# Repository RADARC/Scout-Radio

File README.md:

# Scout-Radio
Si4732 and Raspberry Pi Pico Radio device for Scouts to build and use to gain badges

Reading and District Amateur Radio Club works withl local Scouts groups and help them in support of their badges and activities

## Objectives:
<ul>
<li>Design and build a radio device with can support Scouts in the following badges
<ul>
<li>[Electronics](https://www.scouts.org.uk/scouts/activity-badges/electronics/)</li>
<li>[Communicator](https://www.scouts.org.uk/scouts/activity-badges/communicator/)</li>
</ul>
<li>Involve Scouts in radio activities</li>
<li>Potential Sponsorship and incresaed local community technology support for Scouts</li>
<li>Interesting Project for RADARC Constructors</li>
<li>Have Fun!</li>
</ul>

## Design Specification
Derived from the RLab Reading Hackspace [Project Athena](https://github.com/reading-hackspace/project-athena)
<ul>
<li>Microprocessor design based on Raspberry Pi Pico Microcontroller</li>
<li>Programmable firmware in CircuitPython and other programming languages via USB</li>
<li>On Board AM and FM Radio</li>
<li>Loudspeaker and audio output</li>
<li>Rotary Encoder and control buttons</li>
<li>Battery powered 3 off AAA, or LiPo with on board charger from USB</li>
<li>Audio output jack</li>
<li>Mixture of surface mount and through hole components. Some components can be factory assembled</li>
<li>Colour LCD display integral</li> 
<li>Optional GPS module</li>
<li>Optional Compass module</li>
<li>Low Cost, under £20</li>
</ul>

## Proposed Design
The following elements are in the prototype design, being commonly available at reasonable cost. Some of these may not be in the final design or optional modules to save cost:

### Raspberry Pi Pico Processor Module

The Raspberry Pi Pico module is based on the RP2040 microprocessor. The module includes flash memory, power supply, crystal clock and a USB interface. It is an easy way to to integrate this processor without detail PCB layout and at attractive cost.
The Pi Pico Module have different variants which are pin compatible. They offer different USB Connectors(Micro-B, USB-C), Wireless and bluetooth integrated, and a higher performance version in the RP2350.
[Pi Pico Data sheet](https://datasheets.raspberrypi.com/pico/pico-datasheet.pdf)

The RP2040 is an ARM Cortex M0+ 32 bit processor which operates at 133MHz and includes a wide range of integrated peripherals.
[RP2040 Data sheet](https://datasheets.raspberrypi.com/rp2040/rp2040-datasheet.pdf)

High quality software support for the RP2040 and Pi Pico Modules is available in C/C++ ([C SDK](https://www.raspberrypi.com/documentation/microcontrollers/c_sdk.html), and [Arduino Pi Pico](https://www.tomshardware.com/how-to/program-raspberry-pi-pico-with-arduino-ide)), and Python([Micropython](https://www.raspberrypi.com/documentation/microcontrollers/micropython.html), and [CircuitPython](https://circuitpython.org/board/raspberry_pi_pico/))

### SiLabs Si4732 AM/FM radio
[Datasheet](https://www.skyworksinc.com/-/media/Skyworks/SL/documents/public/data-shorts/Si4732-A10-short.pdf)

The Si4732 is an integrated AM/FM radio device which is digitally programmable over I2C.
It covers a range of frequencies:
<ul> 
<li>Worldwide FM band support (64–108 MHz) </li>
<li>Worldwide AM band support (520–1710 kHz)</li>
<li>SW band support (2.3–26.1 MHz)</li>
<li>LW band support (153–279 kHz)</li>
</ul>
The radio also supports FM stereo and RDS.
Software patches are available for the device to support SSB and NBFM

### Rotary Encoder and push button controls

A side operated rotary encoder is installed on the prototype, but we might look at lower cost alternatives. There are 6 tactile push button switches which can be used to invoke the various radio functions. These controls can also be used to play simple nintendo like games on the radio.

### Audio Output
The stereo audio audio output from the radio chip is amplified to provide an output to headphones of external speakers. This is then further amplified to drive an on board loudspeaker.
The output from the radio chip is also fed to the ADC inputs on the Pi Pico to enable the Pi Pico to provide USB or Bluetooth feed to an external program such as WSJT-X. The Pi Pico may be able to decode locally digital protocols such as FT8 and display locally.
The Pi Pico also provides a PWM audio output for beeps, morse code, and music for simple games.

### 1.3 inch IPS Colour LCD Display

A colour LCD display was chosen for the device. Limited space allows for a [240 by 240 pixel 1.3 inch IPS display](https://www.smart-prototyping.com/1_3-inch-TFT-IPS-Display-Module-ST7789-SPI-240-240).
The module is based on the ST7789 display IC and is supported by both Micropython and CircuitPython grahics libraries.

### Torch

A high intensity white LED is provided under processor control to be used as a torch or for visual signalling.

### Compass Option

An optional compass module based on the LSM303 magnetometer, Compass and accelerometer device can be fitted.

### GPS Option

An optional GPS module based on the ATGM336H GPS receiver can be fitted 

## Costs
The following costs are based on the JLCPCB prototype build of five units.
All costs are in UK pounds and include shipping and taxes

### Component Costs
| Item      | Cost £      |
|-----------|-----------|
|Placed components| 8.68| 
|Unplaced components| 8.44|
||--------|
|Total £| 17.12|

The above component cost includes PCB, SMT components, Pi Pico, display and all switches and connectors. I does not include a case.
The placed components were placed by JLCPCB. This cost is dominated by the radio chip and rotary encoder, better sourcing could easily get the component cost under £15.

### Optional Components
| Item       | Cost £    |
|---|---|
|LiPo Battery | 2.1|
|SMA antenna| 2.59|
|Compass module| 2.75|
|GPS Module|  2.92      |

### Build Costs
The build costs are again based on the five off prototype, so maybe not very representative of a larger batch. I excluded from the build the through hole components to save cost, also a couple of components that they did not have in stock.
Build costs are driven by a mix of fixed costs per order, setup, solder stencil, etc. Also Costs per board and joint.There are then costs related to what components are used. Common components are already mounted on the pick and place machine and have low cost per component ( fraction of cent). Less common components are often low cost, but we pay $3 per component type to load the component spool to the pick and place, this cost often dominates the assembly costs.
Assembly of through hole components and components and edge mounted components is possible but would attract increased cost.

For the five prototypes:

The placed component costs can be excluded, so $44.32 for five. With tax and shipping this is £11.08 per board. Rather expensive at prototype level, but for for a decent board volume (25) when I run through the pricing calculator I get £2.20 per board.

## PCB Files

## Installing Software
``` reinstallsys.sh ```
installs a system from scratch including Circuit Python. Runs on linux only atm.

## Software Project Plan, 12th March 2025.
Tasks are either small, medium or large (S/M/L)

In priority order:
* Sort out test code and harness for si4735 driver (done)
* Design and implement a software installation process for target hardware, automating wherever possible (M, done)
* Document possible use cases (M)
* Provide example higher level libraries and applications (M)
* Design and implement standalone POST/BIST for target hardware (M)
* Design and implement production test software. Possibly involves use of
  laptop. Scouts need to know if what they have built works :-) (M)

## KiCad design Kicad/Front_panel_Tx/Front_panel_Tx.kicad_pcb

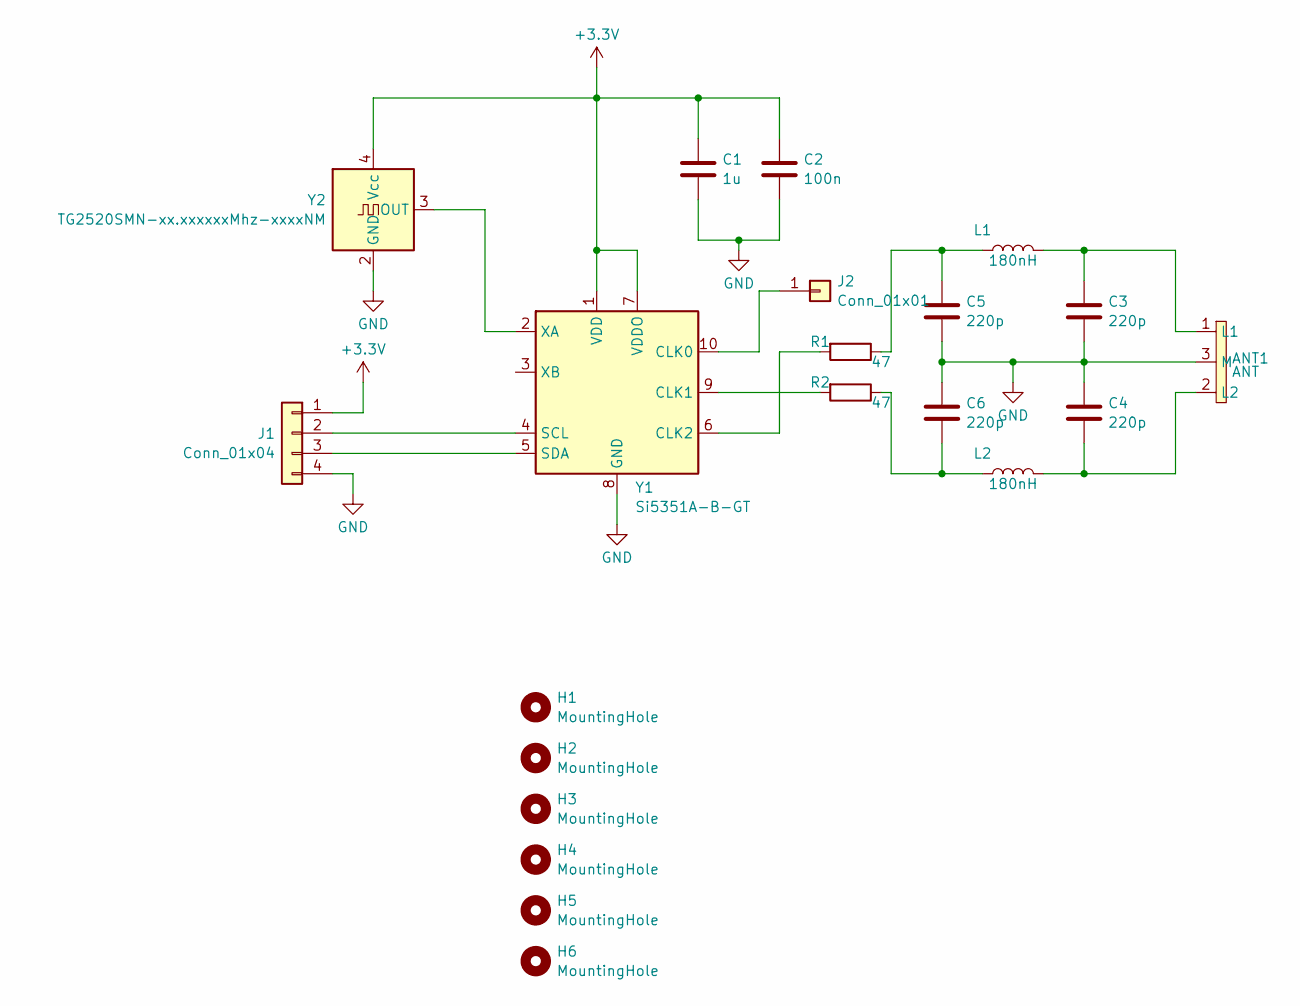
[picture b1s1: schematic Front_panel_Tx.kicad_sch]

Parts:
ANT1: ANT; RFID_Antenna
C1: 1u; C_0603_1608Metric
C2: 100n; C_0603_1608Metric
C3, C4, C5, C6: 220p; C_0603_1608Metric
H1, H2, H3, H4, H5, H6: MountingHole; MountingHole_2.1mm
J1: Conn_01x04; JST_SH_BM04B-SRSS-TB_1x04-1MP_P1.00mm_Vertical
J2: Conn_01x01; TestPoint_Pad_1.5x1.5mm
L1, L2: 180nH; L_0603_1608Metric
R1, R2: 47; R_0603_1608Metric
Y1: Si5351A-B-GT; MSOP-10_3x3mm_P0.5mm
Y2: TG2520SMN-xx.xxxxxxMhz-xxxxNM; Oscillator_SMD_SeikoEpson_TG2520SMN-xxx-xxxxxx-4Pin_2.5x2.0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

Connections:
+3.3V: C1.1, C2.1, J1.1, Y1.1 (VDD), Y1.7 (VDDO), Y2.4 (Vcc)
GND: ANT1.3 (M), C1.2, C2.2, C3.2, C4.1, C5.2, C6.1, J1.4, Y1.8 (GND), Y2.2 (GND)
unnamed: ANT1.1 (L1), C3.1, L1.2
unnamed: ANT1.2 (L2), C4.2, L2.2
unnamed: C5.1, L1.1, R1.1
unnamed: C6.2, L2.1, R2.1
unnamed: J1.2, Y1.4 (SCL)
unnamed: J1.3, Y1.5 (SDA)
unnamed: J2.1, Y1.10 (CLK0)
unnamed: R2.2, Y1.9 (CLK1)
unnamed: R1.2, Y1.6 (CLK2)
unnamed: Y1.2 (XA), Y2.3 (OUT)

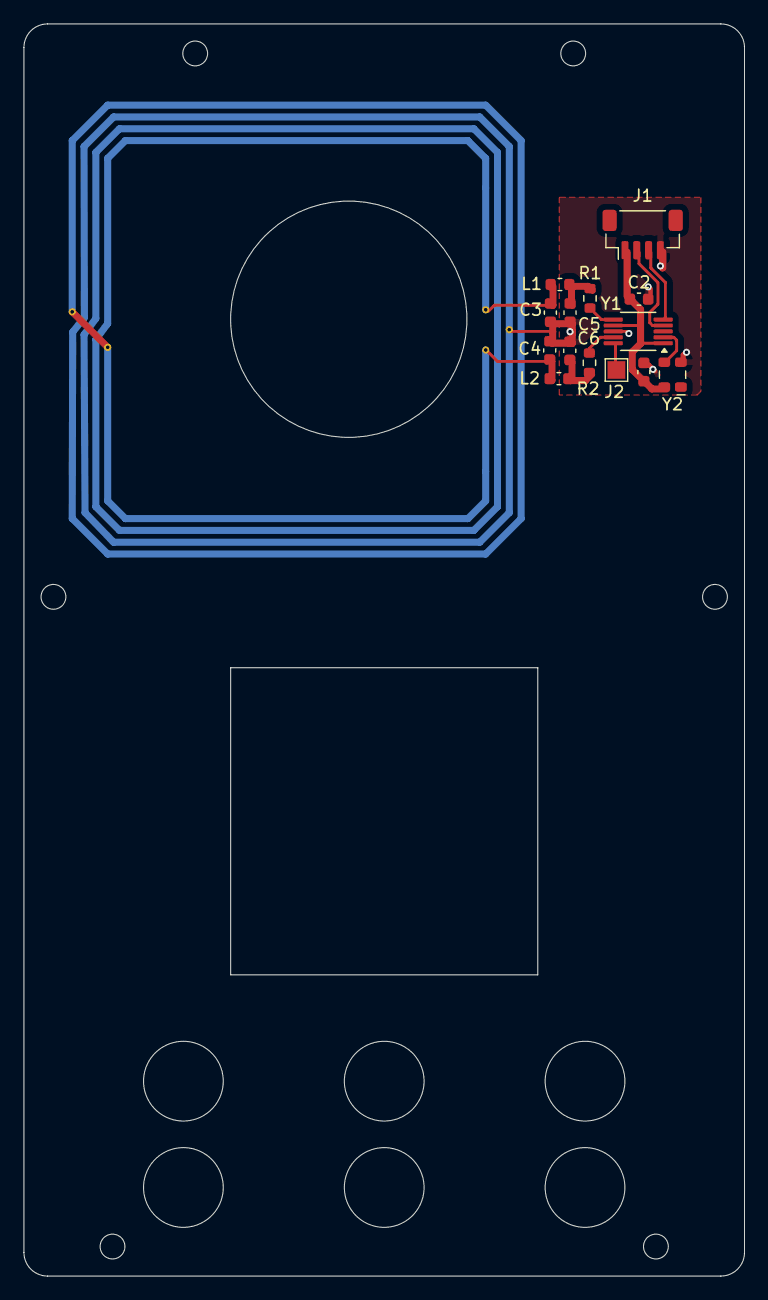
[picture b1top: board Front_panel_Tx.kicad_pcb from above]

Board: 2 copper layers, 61.0 x 106.0 mm, 21 parts (1 on the bottom side), 12 nets.

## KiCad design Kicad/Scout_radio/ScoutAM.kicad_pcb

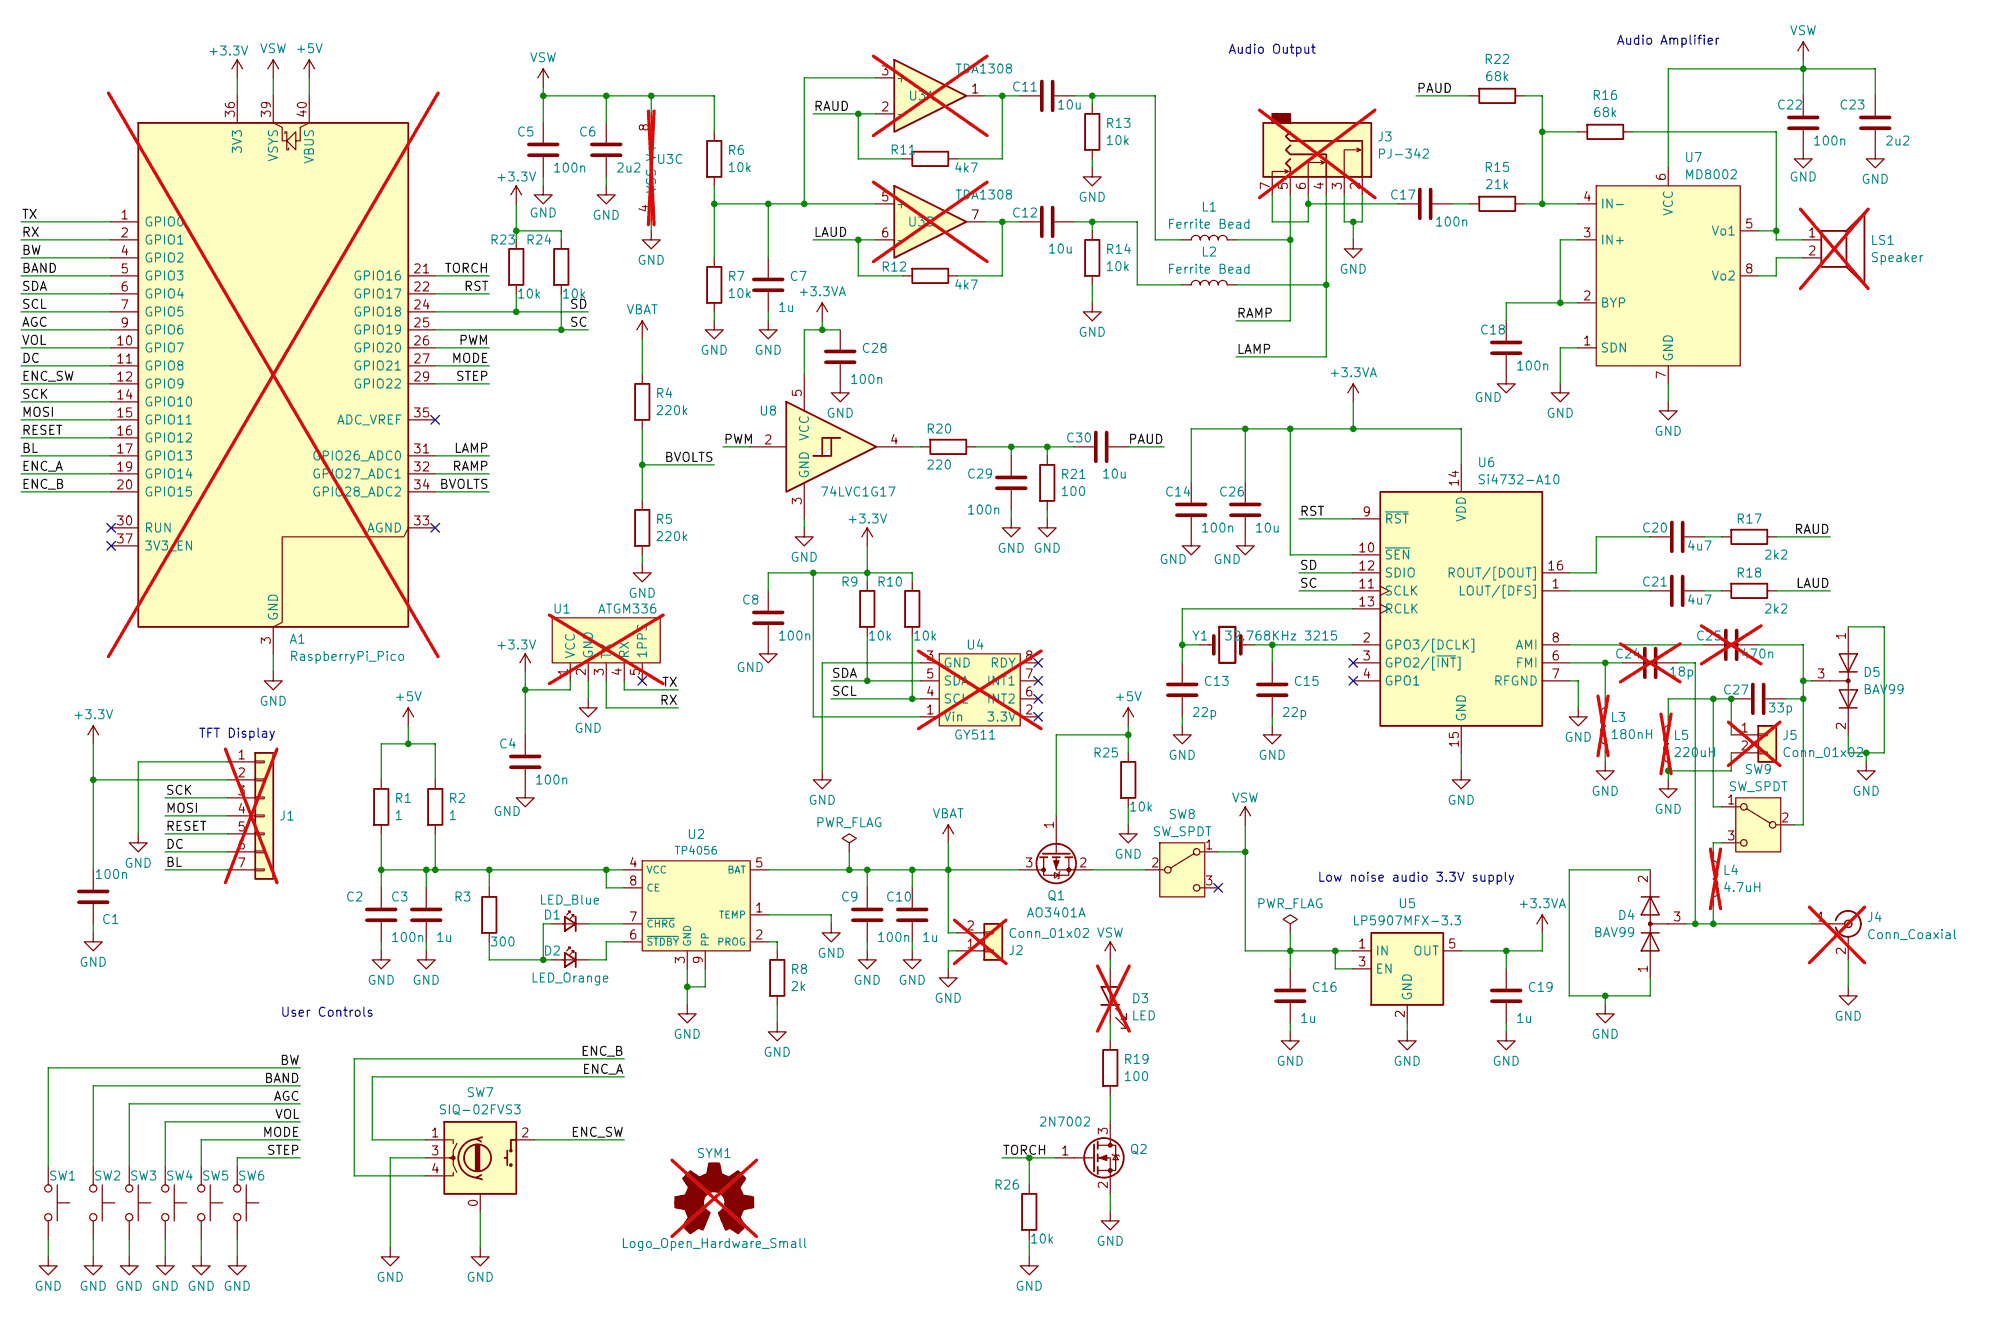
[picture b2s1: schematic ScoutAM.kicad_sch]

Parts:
A1: RaspberryPi_Pico; RPi_Pico_SMD_TH; not fitted
C1, C2, C4, C5, C8, C9, C14, C17, C18, C22, C28, C29: 100n; C_0603_1608Metric; LCSC C14663
C3, C7, C10, C16, C19: 1u; C_0603_1608Metric
C6, C23: 2u2; C_0603_1608Metric
C11, C12, C26, C30: 10u; C_0603_1608Metric
C13, C15: 22p; C_0603_1608Metric
C20, C21: 4u7; C_0603_1608Metric
C24: 18p; C_0603_1608Metric; not fitted
C25: 470n; C_0603_1608Metric; not fitted
C27: 33p; C_0603_1608Metric
D1: LED_Blue; LED_0603_1608Metric
D2: LED_Orange; LED_0603_1608Metric
D3: LED; LED_D5.0mm_Horizontal_O6.35mm_Z9.0mm; not fitted
D4, D5: BAV99; SOT-23
J1: Conn_01x07; 240LCD; not fitted
J2: Conn_01x02; JST_PH_S2B-PH-SM4-TB_1x02-1MP_P2.00mm_Horizontal; not fitted
J3: PJ-342; Jack_3.5mm_PJ342_Horizontal; not fitted
J4: Conn_Coaxial; SMA_Samtec_SMA-J-P-H-ST-EM1_EdgeMount; not fitted
J5: Conn_01x02; PinHeader_1x02_P2.54mm_Horizontal; not fitted
L1, L2: Ferrite Bead; L_0603_1608Metric
L3: 180nH; L_0603_1608Metric; not fitted
L4: 4.7uH; L_0603_1608Metric; not fitted
L5: 220uH; L_0603_1608Metric; not fitted
LS1: Speaker; 30mm_Speaker; not fitted
Q1: AO3401A; SOT-23
Q2: 2N7002; SOT-23
R1, R2: 1; R_0805_2012Metric
R3: 300; R_0603_1608Metric
R4, R5: 220k; R_0603_1608Metric
R6, R7, R9, R10, R13, R14, R23, R24, R25, R26: 10k; R_0603_1608Metric
R8: 2k; R_0603_1608Metric
R11, R12: 4k7; R_0603_1608Metric
R15: 21k; R_0603_1608Metric
R16, R22: 68k; R_0603_1608Metric
R17, R18: 2k2; R_0603_1608Metric
R19: 100; R_2512_6332Metric
R20: 220; R_0603_1608Metric
R21: 100; R_0603_1608Metric
SW1, SW2, SW3, SW4, SW5, SW6: B3FS; SW_Push_1P1T_NO_6x6mm_H9.5mm
SW7: SIQ-02FVS3; SIQ-02FVS3_Rotary_Encoder
SW8, SW9: SW_SPDT; SW_Slide_SPDT_Angled_CK_OS102011MA1Q
SYM1: Logo_Open_Hardware_Small; OSHW-Logo_11.4x12mm_SilkScreen; not fitted
U1: ATGM336; not fitted
U2: TP4056; SOIC-8-1EP_3.9x4.9mm_P1.27mm_EP2.29x3mm
U3: TDA1308; SO-8_3.9x4.9mm_P1.27mm; not fitted
U4: GY511; not fitted
U5: LP5907MFX-3.3; SOT-23-5
U6: Si4732-A10; SOIC-16_4.55x10.3mm_P1.27mm
U7: MD8002; SO-8_3.9x4.9mm_P1.27mm
U8: 74LVC1G17; SOT-23-5
Y1: 32.768KHz 3215; Crystal_SMD_3215-2Pin_3.2x1.5mm

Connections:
+3.3V: A1.36 (3V3), C1.2, C4.1, C8.1, J1.2, R9.1, R10.1, R23.1, R24.1, U1.1 (VCC), U4.1 (Vin)
+3.3VA: C14.1, C19.1, C26.1, C28.1, U5.5 (OUT), U6.10 (~SEN), U6.14 (VDD), U8.5 (VCC)
+5V: A1.40 (VBUS), Q1.1 (G), R1.1, R2.1, R25.1
/AGC: A1.9 (GPIO6), SW3.1
/BAND: A1.5 (GPIO3), SW2.1
/BL: A1.17 (GPIO13), J1.7
/BVOLTS: A1.34 (GPIO28_ADC2), R4.2, R5.1
/BW: A1.4 (GPIO2), SW1.1
/DC: A1.11 (GPIO8), J1.6
/ENC_A: A1.19 (GPIO14), SW7.1 (A)
/ENC_B: A1.20 (GPIO15), SW7.4 (B)
/ENC_SW: A1.12 (GPIO9), SW7.2 (S1)
/LAMP: A1.31 (GPIO26_ADC0), J3.4, L2.2
/LAUD: R12.2, R18.1, U3.6 (-)
/MODE: A1.27 (GPIO21), SW5.1
/MOSI: A1.15 (GPIO11), J1.4
/PAUD: C30.1, R22.2
/PWM: A1.26 (GPIO20), U8.2
/RAMP: A1.32 (GPIO27_ADC1), J3.5, L1.2
/RAUD: R11.2, R17.1, U3.2 (-)
/RESET: A1.16 (GPIO12), J1.5
/RST: A1.22 (GPIO17), U6.9 (~RST)
/RX: A1.2 (GPIO1), U1.3 (TX)
/SC: A1.25 (GPIO19), R24.2, U6.11 (SCLK)
/SCK: A1.14 (GPIO10), J1.3
/SCL: A1.7 (GPIO5), R10.2, U4.4 (SCL)
/SD: A1.24 (GPIO18), R23.2, U6.12 (SDIO)
/SDA: A1.6 (GPIO4), R9.2, U4.5 (SDA)
/STEP: A1.29 (GPIO22), SW6.1
/TORCH: A1.21 (GPIO16), Q2.1 (G), R26.1
/TX: A1.1 (GPIO0), U1.4 (RX)
/VOL: A1.10 (GPIO7), SW4.1
GND: A1.3 (GND), A1.8 (GND), A1.13 (GND), A1.18 (GND), A1.23 (GND), A1.28 (GND), A1.38 (GND), C1.1, C2.2, C3.2, C4.2, C5.2, C6.1, C7.2, C8.2, C9.2, C10.2, C13.2, C14.2, C15.2, C16.2, C18.2, C19.2, C22.2, C23.1, C26.2, C28.2, C29.2, D4.1 (K), D4.2 (A), D5.1 (K), D5.2 (A), J1.1, J2.1, J3.2, J3.3, J4.2 (Ext), J5.2, L3.1, L5.1, Q2.2 (S), R5.2, R7.2, R8.2, R13.2, R14.2, R21.2, R25.2, R26.2, SW1.2, SW2.2, SW3.2, SW4.2, SW5.2, SW6.2, SW7.0 (MP), SW7.3 (C), U1.2 (GND), U2.1 (TEMP), U2.3 (GND), U2.9 (PP), U3.4 (VSS), U4.3 (GND), U5.2 (GND), U6.7 (RFGND), U6.15 (GND), U7.1 (SDN), U7.7 (GND), U8.3 (GND)
unnamed: C11.1, L1.1, R13.1
unnamed: C11.2, R11.1, U3.1
unnamed: C12.1, L2.1, R14.1
unnamed: C12.2, R12.1, U3.7
unnamed: C17.1, R15.2
unnamed: C17.2, J3.6, J3.7
unnamed: C20.1, R17.2
unnamed: C21.1, R18.2
unnamed: C29.1, C30.2, R20.1, R21.1
unnamed: D1.2 (A), D2.2 (A), R3.2
unnamed: D1.1 (K), U2.7 (~CHRG)
unnamed: D2.1 (K), U2.6 (~STDBY)
unnamed: D3.1 (K), R19.1
unnamed: C24.1, D4.3 (K), J4.1 (In), L4.2
unnamed: C27.2, J5.1, L5.2, SW9.1 (A)
unnamed: Q1.2 (S), SW8.2 (B)
unnamed: Q2.3 (D), R19.2
unnamed: R20.2, U8.4
unnamed: C25.1, C27.1, D5.3 (K), SW9.2 (B)
unnamed: L4.1, SW9.3 (C)
unnamed: C2.1, C3.1, R1.2, R2.2, R3.1, U2.4 (VCC), U2.8 (CE)
unnamed: R8.1, U2.2 (PROG)
unnamed: C7.1, R6.2, R7.1, U3.3 (+), U3.5 (+)
unnamed: C25.2, U6.8 (AMI)
unnamed: C24.2, L3.2, U6.6 (FMI)
unnamed: C15.1, U6.2 (GPO3/[DCLK]), Y1.2
unnamed: C21.2, U6.1 (LOUT/[DFS])
unnamed: C13.1, U6.13 (RCLK), Y1.1
unnamed: C20.2, U6.16 (ROUT/[DOUT])
unnamed: C18.1, U7.2 (BYP), U7.3 (IN+)
unnamed: R15.1, R16.2, R22.1, U7.4 (IN-)
unnamed: LS1.1, R16.1, U7.5 (Vo1)
unnamed: LS1.2, U7.8 (Vo2)
VBAT: C9.1, C10.1, J2.2, Q1.3 (D), R4.1, U2.5 (BAT)
VSW: A1.39 (VSYS), C5.1, C6.2, C16.1, C22.1, C23.2, D3.2 (A), R6.1, SW8.1 (A), U3.8 (V+), U5.1 (IN), U5.3 (EN), U7.6 (VCC)

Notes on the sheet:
Audio Amplifier
Audio Output
TFT Display
Low noise audio 3.3V supply
User Controls

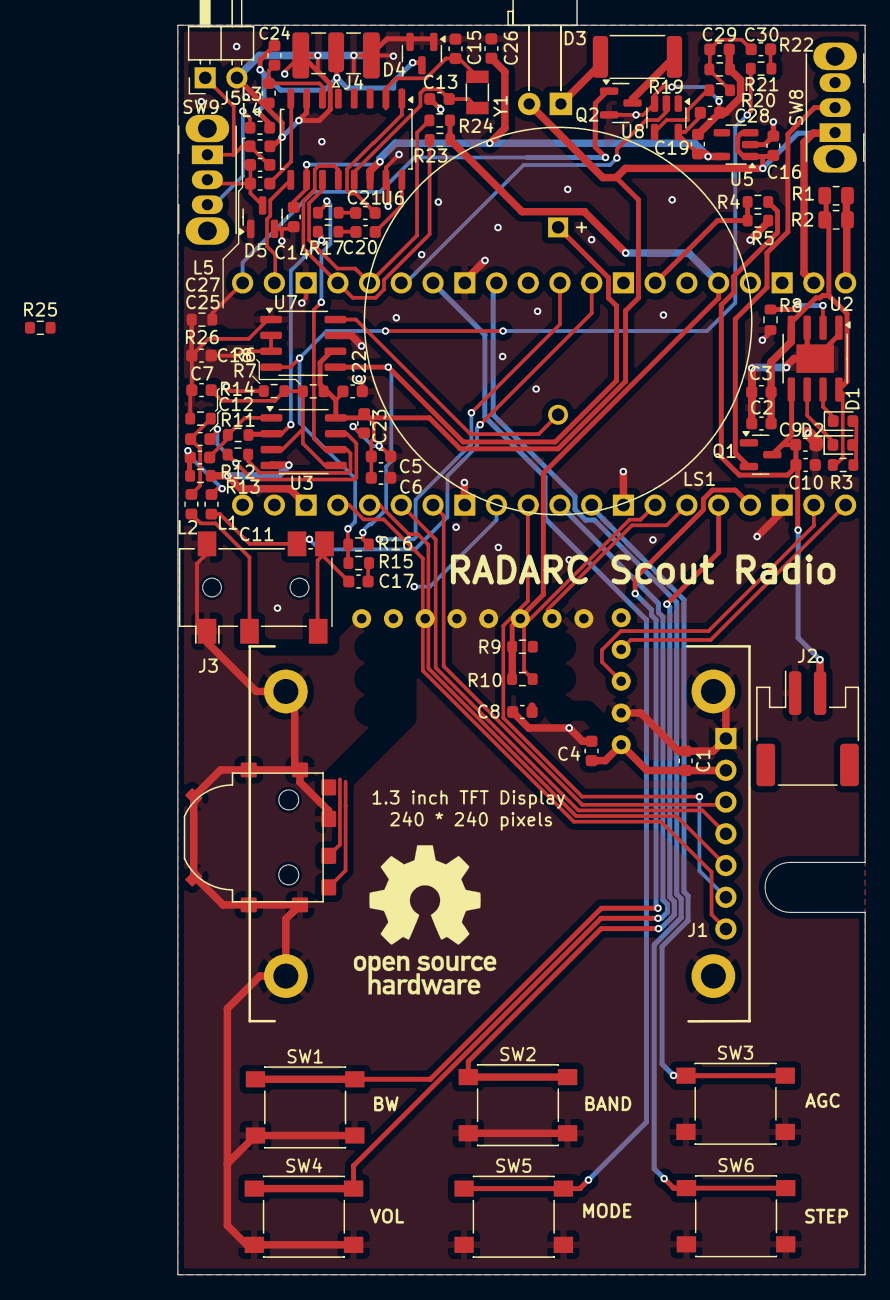
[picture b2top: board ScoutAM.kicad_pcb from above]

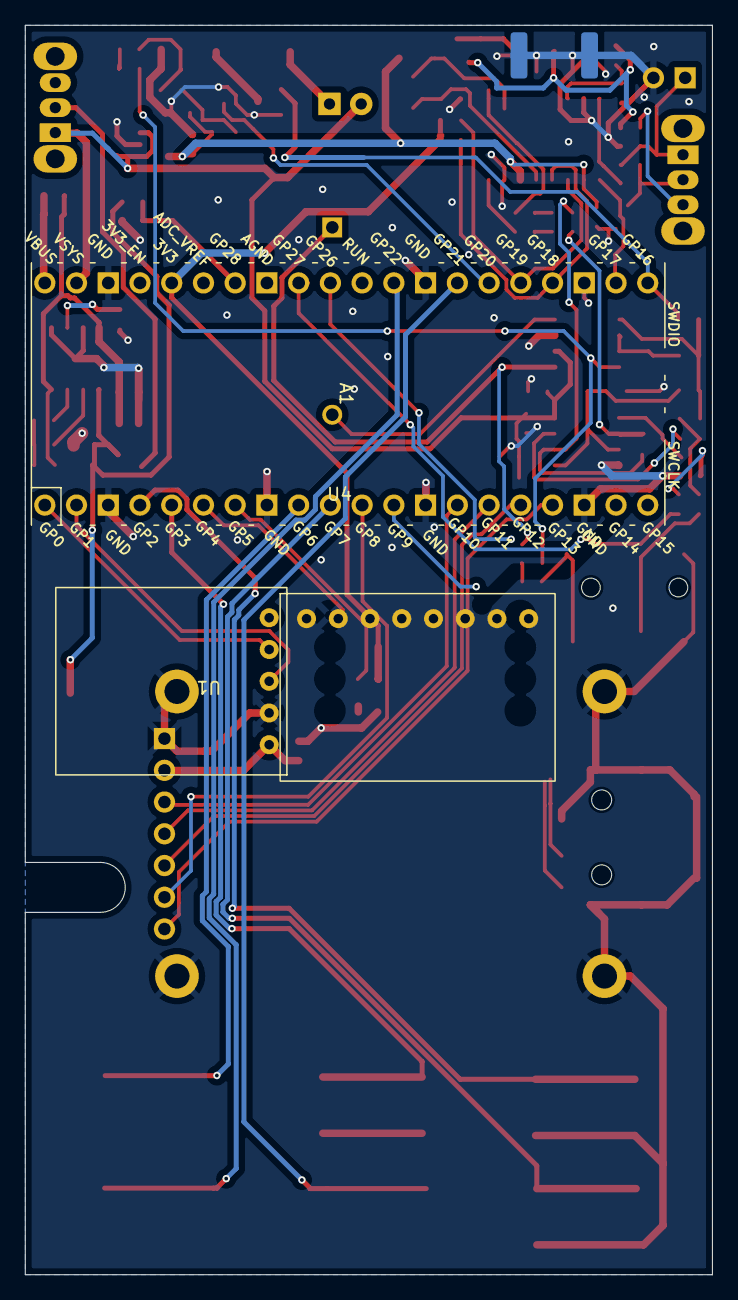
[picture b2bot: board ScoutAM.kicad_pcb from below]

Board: 2 copper layers, 55.0 x 100.0 mm, 94 parts (3 on the bottom side), 68 nets.

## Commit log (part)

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2024-11-30 First commit of Kicad files
2024-11-30 Update README.md to include GPS and compass
2024-12-02 Added cost information to README.md
2024-12-12 Added software folder
    Added software folder with CircuitPython for testing
    Fixed hardware cross of SDA and SCL to Si4732
2024-12-14 Tidy Up Software folders
    Add folders to software
    Add GPS tests
    Add Magnetometer and accelerometer tests
    Add Morse sending
2025-02-04 update to latest si4735 driver from RADARC si4735 repo
2025-02-07 software project 'plan'
2025-02-07 add sizing
2025-02-14 Added unit test code
2025-02-24 update to latest from si4735 repo - future dev will happen here
2025-02-24 fix/bodge source location for si4735 python stuff
2025-02-25 Front end implementation
2025-02-25 Added encoder for tuning
2025-02-25 Added bandwidth
2025-02-26 Added AM & USB/LSB
2025-02-26 SSB/LSB testing
2025-02-26 debug setFrequency
2025-02-26 Fixed sideband
2025-03-10 remove duplicate code
2025-03-10 factor out FileOPs objects for Circuit Python and Micro Python
2025-03-10 bomb on failure immediately with sysinstall
2025-03-11 cleanup; fix some pylint whining
2025-03-11 pylint
2025-03-11 make reboot method on testboard a thing
2025-03-11 cleanup (switch sense of test to be positive), bomb early if source file doesn't exist, comments
2025-03-11 docstrings, reference self to shut up pylint
2025-03-11 start to make installation of code.py optional at top level
2025-03-11 fix ensuredir etc. for Micro Python; beginnings of copy files from target to source
2025-03-11 make provision for code.py at top level not coming back to >>> repl prompt
2025-03-11 more on --revsync
2025-03-11 add missing file install.py at top level which installs code.py typically
2025-03-11 shuffle FileOPs objects around in source file; comments for TestBoard derived objects
2025-03-11 lose a couple of lines
2025-03-11 remove some duplicated code
2025-03-11 pylint stuff for top level things
2025-03-11 factor out loop invariant
2025-03-11 factor out calculation of target_homedir into a member variable
2025-03-11 factor out get_target_fullpath method avoiding duplicated code
2025-03-11 tweaks (fixes) to allow testboard.py to be run standalone
2025-03-11 pylint thinks TestBoard object is getting fat. It's probably right. Make verbose member variable module scope. No real reason for it to be a member.
2025-03-11 whitespace
2025-03-11 add admission of guilt
2025-03-11 case consistency
2025-03-11 beginnings of installer for GPS - doesn't work due to adafruit_gps not being found
2025-03-11 installer for LSM303 component
2025-03-11 comment
2025-03-11 readability
2025-03-11 factor out file fileops.py
2025-03-11 factor out boarddetect.py file from testboard.py
2025-03-11 better naming, I've used boarddetect elsewhere...
2025-03-11 fix, pylint
2025-03-11 use new si4735_CP creation interface
2025-03-11 don't want __pycache__ in git
2025-03-11 improve verbose printing control: beginnings of proper logging
2025-03-11 pylint for sysinstall
2025-03-12 implement TODO get rid of self.i2c
2025-03-12 Micro Python - be friendly if tshell is not installed
2025-03-12 add info about uctypes
2025-03-12 simplify pylint whine workarounds
2025-03-12 add comment for idea of introducing --app option on install.py's
2025-03-12 Added menu folder
2025-03-14 fix setting of directory on target
2025-03-16 split out setting of home directory from setfiles (files to be installed on target) allowing files on target to be tested unmodified
2025-03-16 move formatoutput to a central place, for now testboard
2025-03-16 only write to flash if necessary i.e. only copy on files if they don't exist on target or there is a difference. Might help with flash getting trashed occasionally.
2025-03-16 add --install option to test.py
2025-03-16 better comment
2025-03-16 remove unused variable
2025-03-16 add run.py - test.py without the test slant. Useful for dev work?
2025-03-16 comments
2025-03-16 fix comment
2025-03-16 rename radio.scout.py to radioapp.py
2025-03-16 fix paren
2025-03-16 change how serial port usage is done for MicroPython. Make it the same as CircuitPython switching to rshell app when we need to.
2025-03-16 remove unnecessary import os and os.chdir
2025-03-16 more example code in run.py
2025-03-16 fix hideous bug
2025-03-16 minor pylint whines
2025-03-16 method to start app on power up automatically, code.py main.py etc.
2025-03-16 fix auto run file member variable
2025-03-16 be just a bit nice
2025-03-16 shell script to help installing RPI-Pico
2025-03-16 don't start app by default
2025-03-16 pylint; comment
2025-03-16 runfile for Morse
2025-03-16 fix quotes
2025-03-16 create a flash directory for initial target python installation
2025-03-16 tweak to README
2025-03-17 fix README
2025-03-17 basic README
2025-03-17 better progress text
2025-03-17 slight optimisation
2025-03-17 pylint - useless sendrepl on circuit python board
2025-03-17 fix missing files
2025-03-17 simple run.py for LSM303
2025-03-17 add simple serial monitor function
2025-03-17 use our own method to close serial port
2025-03-17 fix initial CTRLC, return a string already decoded from send_repl
2025-03-17 add warning
2025-03-17 linux only disclaimer for now
2025-03-17 make it clear code.py is deprecated/unused; continues in Radio component as radioapp.py or similar
2025-03-17 Added intermediate radio object
2025-03-17 type consistency; fix comment
2025-03-17 Added missing self
2025-03-17 fix duff comment
2025-03-18 cruft removal, I think.
2025-03-18 add admission of guilt/comment
2025-03-18 micropython fix
2025-03-18 deal with MicroPython reboot behaviour being different to CircuitPython. Stop sendrepl echoing the command in its output.
2025-03-18 fix bug where pexpect gets confused after installing files on MicroPython. Not fully understood. Flush serial port when opening it. Reboot on MicroPython after installing files as we don't know what 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
2025-03-18 i2c patch download speed investigation: addi explicit speeds to i2c
2025-03-18 start to enforce some correctness
2025-03-18 remove useless fw version printing
2025-03-18 Revert "remove useless fw version printing"
    This reverts commit 968ff2db444d9c0b3ad1485090b0a1ae300c2647.
2025-03-18 add a final report of firmware version after downloading the patch
2025-03-18 fix identify
2025-03-18 wait for circuit python filesystem to come up rather than failing miserably
2025-03-18 Testing patch in code
2025-03-18 wait a bit longer for circuit python filesystem
2025-03-18 improve some nastiness in testboard. Less nasty, perhaps.
2025-03-18 testboard on a diet
2025-03-19 implement so called compressed patch download - patch doesn't seem to work
2025-03-19 investigate using binary file
2025-03-19 introduce MIN_DELAY_WAIT_DLPATCH
2025-03-19 possibly useful for simon - implementation of compressed download using patch embedded in python but board hangs
2025-03-19 target hangs
2025-03-19 simplify
2025-03-19 compressed binary implementation
2025-03-19 tidy
2025-03-19 confirmed working
2025-03-19 utility to create patchcomp.bin from patch.csg
2025-03-19 no longer hangs
2025-03-19 test the short SSB patch - doesn't seem to work
2025-03-19 sanitise a bit
2025-03-19 add option to run either compressed or no
2025-03-19 performs reasonably now
2025-03-19 fix performance problems: take the sleeps out
2025-03-19 we do need a sleep, needs further work. Tidy up.
2025-03-19 remove noise from patchPowerUp
2025-03-19 introduce MIN_DELAY_WAIT_DLPATCH so we can tweak patch download i2c wait independently
2025-03-19 fix test of firmware version running
2025-03-19 shebang, executable perm
2025-03-19 fix output from sendrepl. Don't destroy formatting done with CR/LF but still keep the final result stripped (for now)
2025-03-19 add note about patchcomp.bin
2025-03-19 use download_compressed_patch by default
2025-03-19 tidy, whitespace, testcmppatchdownload.py now superceded by testpatchdownload.py
2025-03-19 naming
2025-03-19 add --app flag
2025-03-19 don't mess with a sleep we don't fully understand...yet. Unused anyway now.
2025-03-20 naming, get rid of a range call
2025-03-20 seems faster running testpatchdownload.py
2025-03-20 run i2c at 1MHz in tests
2025-03-20 add progress comment
2025-03-20 introduce runlib
2025-03-20 use runlib in all the various app run.pys
2025-03-20 add progress text
2025-03-20 Test overclock
2025-03-20 add advice if patchcomp.bin does not exist
2025-03-20 microcontroller overclock circuit python only
2025-03-20 Done PR
2025-03-20 remove downloadPatch - unused
2025-03-20 get rid of top level install.py - confusing
2025-03-20 rename si4735_CP.py, cleanup
2025-03-20 Cleanup whitepace
2025-03-20 friendlyise
2025-03-20 cleanup
2025-03-20 handy hint
2025-03-20 slightly better idiom
2025-03-20 radio_rx and RADIO_RX -> radio and RADIO
2025-03-20 fixed RADIO. error
2025-03-20 guidance
2025-03-20 Added volume control
2025-03-20 Fix broken SSB bandwidth
2025-03-20 Si4735test -> Si47xxtest
2025-03-20 setSSBAudioBandwidth->setSSBBandwidth
2025-03-20 pylint, fix tests a bit
2025-03-20 test.py -> si47xx_test.py, testpatchdownload.py -> si47xx_testpatchdownload.py as these test files are testing si47xx.py. Both run on Micro Python and Circuit Python ok.
2025-03-20 add crude micro python installer
2025-03-20 for circuit python, unconditionally remove code.py when tools in use. Perhaps a bit rude but if you're using the tools, you want access to the system.
2025-03-21 improve interaction
2025-03-21 add reinstall.sh
2025-03-21 look for rw mount no longer necessary
2025-03-21 plug a few holes and race conditions
2025-03-21 rename
2025-03-21 naming, sleep less, no need to unplug USB at end
2025-03-21 less wordy progress feedback
2025-03-21 better singleton behaviour
2025-03-21 always reset_input_buffer() on serial open
2025-03-21 factor out autorunfile_name
2025-03-21 work around odd initial condition with serial on Micro Python
2025-03-21 clean up tests a bit
2025-03-21 fix up si47xx tests to use singleton board, simplify a bit, add beginnings of radio_test.py
2025-03-21 another test
2025-03-21 cruft removal
2025-03-21 add timing of download and test it is less than 1.5 seconds
2025-03-21 remove double check
2025-03-21 placeholder license
2025-03-21 lose execute perm
2025-03-21 minor optimisation
2025-03-21 Revert "minor optimisation"
    This reverts commit 5d6c2fed9b526d2dce616b510ab36ce138b99b52.
2025-03-21 remove print and i2c write happening as side effect
2025-03-21 minor tweaks
2025-03-22 beginnings of interaction with minicom
2025-03-22 beginnings of a bitfield thing
2025-03-22 no need to use a bytearray
2025-03-22 installer -> installib
2025-03-22 add ability to specify (i.e. override) app to run from command line rather than what's in a component's run.py
2025-03-22 add --repl to run.py
2025-03-22 more Display test apps
2025-03-22 typo
2025-03-22 factor out close_expect_serial
2025-03-22 add possibly useless option --norun; may be handy to start interaction with target using minicom
2025-03-22 improve help
2025-03-22 add noboot option to run.py - probably useless but who knows. Combined with --minicom could be handy for debug
2025-03-22 make what we can private
2025-03-22 fix return type
2025-03-23 improve minicom hooking
2025-03-23 cleanup of --repl
2025-03-23 admit to reinstallsys.sh
2025-03-24 fix help text
2025-03-24 fix force default value
2025-03-24 factor out a file manager from testboard
2025-03-24 remove a member variable on testboard; simplify
2025-03-24 stuff mountpoint and auto run file in fileops object
2025-03-24 make what we can private in micropython derived test board object
2025-03-24 sendrshell cmd cannot be private - used by fileops
2025-03-25 remove unused not_implemented function
2025-03-25 use self.close_expect_serial made for the job in the base class in the micropython test board. Make it protected in the base class. Fix out of date comments.
2025-03-25 add FLASH OK
2025-03-26 Improving tuning, keep track of frequency
2025-03-26 use argparse and thus add --help; towards issue #10
2025-03-26 pylint: unused arg
2025-03-27 add help/usage/-? text
2025-04-08 create patchcomp.bin automatically if it does not exist from install.py. Tidy up, pylint.
2025-04-11 try and head off a gotcha
